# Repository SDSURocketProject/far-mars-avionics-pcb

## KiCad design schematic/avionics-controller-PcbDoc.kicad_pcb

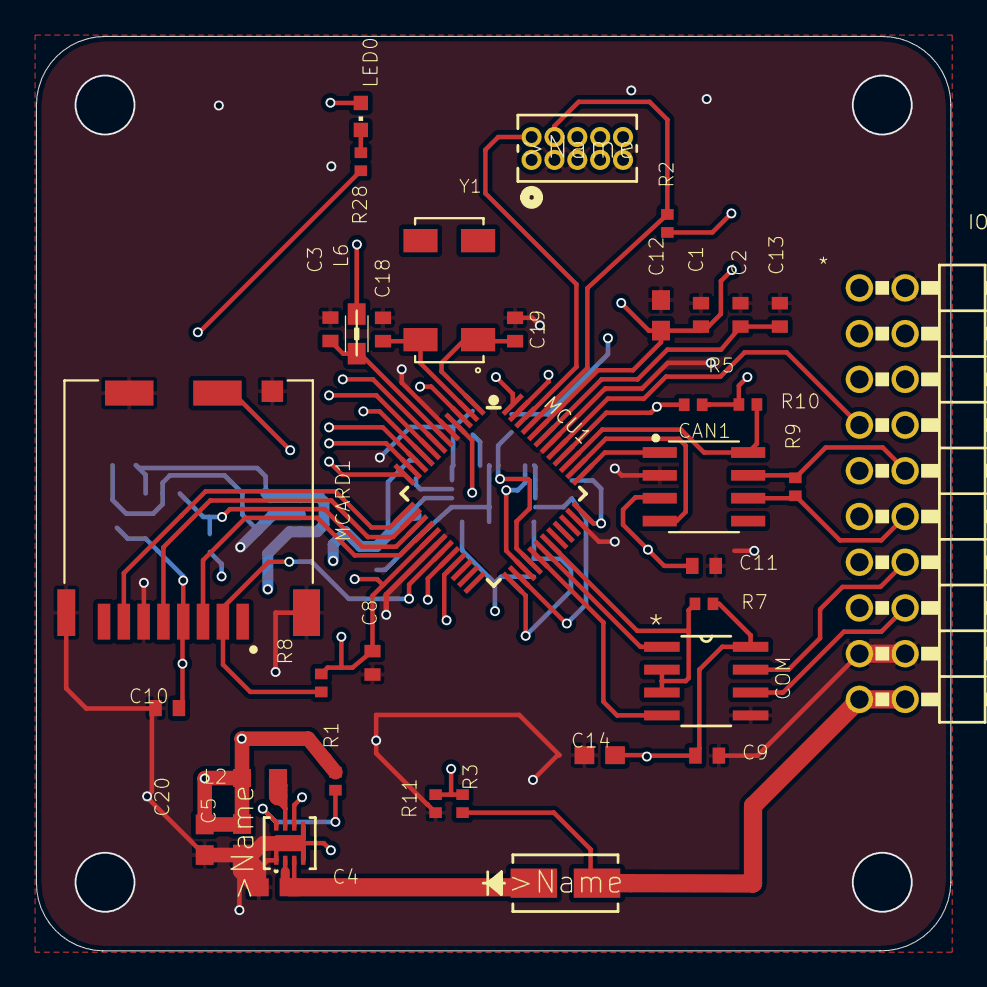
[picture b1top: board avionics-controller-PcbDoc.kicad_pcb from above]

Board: 4 copper layers, 50.8 x 50.8 mm, 52 parts (0 on the bottom side), 51 nets.

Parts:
3VREG1, 3VREG-SD1: 3.3VREGULATOR; SOT95P280X110-5
C1, C2, C3, C8, C9, C10, C11, C15, C16: 100n; C0402
C4, C5, C12, C14, C20: 10u; C0603
C6, C7, C13, C17, C21: 1u; C0402
C18, C19: 15p; C0402
CAN1: MCP2561T-E8SOIC; SOIC127P600X175-8
CR1: B160-13-FSMA-M; SMA-M
IMU1: BNO055; LGA28R50P4X10_380X520X100
IO1: PINHD-2X10_90; 2X10_90
L2: 2.2u; L2012C
L6: MH2029-300Y; 0805
LED0: 2V @ 20mA; CHIPLED_0603
MCARD1: DM3CS-SF; HRS_DM3CS-SF
MCU1: ATSAMC21G18-A; TQFP-48
R1: 100k; R0402
R2, R11, R38, R39: 1k; R0402
R3, R4, R5, R6, R7, R8, R10, R12: 10k; R0402
R9, R28: 120; R0402
REG5V1: TPS62163DSGT; DSG8_1P6X0P9
SWD1: DEBUG-HEADER; CONN_MINITEK_2X5_HDR
U1: SN65HVD10_D_8; D8
U$6: RP-LOGO
Y1: ABS25-32.768KHZ; ABS25-32.768KHZ-6-T

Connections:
3.3V: 3VREG1.5, C6.1, C8.1, C9.1, C14.1, C15.1, IMU1.3, IMU1.28, LED0.A, MCU1.17, MCU1.36, R4.1, R6.1, R7.1, R8.1, R38.1, R39.1, U1.8
5V: 3VREG1.1, 3VREG1.3, 3VREG-SD1.1, C1.1, C5.1, C7.1, C11.1, C12.1, C20.1, C21.1, CAN1.3, IO1.1, L2.2, L6.1, MCU1.44, R1.2, R2.1, R5.1, R10.1, R12.1, REG5V1.6, SWD1.1
/avionics-controller_1/3V_SD: 3VREG-SD1.5, C10.1, C17.1, MCARD1.4
/avionics-controller_1/A: IO1.16, U1.6
/avionics-controller_1/B: IO1.14, U1.7
/avionics-controller_1/CANH: CAN1.7, IO1.10, R9.2
/avionics-controller_1/CANL: CAN1.6, IO1.12, R9.1
/avionics-controller_1/CAN_RX_5V: CAN1.4, MCU1.38
/avionics-controller_1/CAN_STBY_5V: CAN1.8, MCU1.39, R10.2
/avionics-controller_1/CAN_TX_5V: CAN1.1, MCU1.37
/avionics-controller_1/DATA_DIR: MCU1.31, R7.2, U1.2, U1.3
/avionics-controller_1/IMU_INT: IMU1.14, MCU1.27
/avionics-controller_1/IMU_NRST: IMU1.11, MCU1.28, R4.2
/avionics-controller_1/LED0: MCU1.21, R28.1
/avionics-controller_1/MCU_NRST: MCU1.40, R5.2, SWD1.10
/avionics-controller_1/MCU_RX_3.3V: MCU1.30, U1.1
/avionics-controller_1/MCU_TX_3.3V: MCU1.29, U1.4
/avionics-controller_1/PA02/AIN0: IO1.5, MCU1.3
/avionics-controller_1/PA04/AIN4: IO1.9, MCU1.9
/avionics-controller_1/PA05/AIN5: IO1.11, MCU1.10
/avionics-controller_1/PA06/AIN6: IO1.13, MCU1.11
/avionics-controller_1/PA07/AIN7: IO1.15, MCU1.12
/avionics-controller_1/PA16_SER1_I2C_SDA: IMU1.20, MCU1.25, R38.2
/avionics-controller_1/PA17_SER1_I2C_SCL: IMU1.19, MCU1.26, R39.2
/avionics-controller_1/PA28: IO1.7, MCU1.41
/avionics-controller_1/PB02/AIN10: IO1.3, MCU1.47
/avionics-controller_1/PB03/AIN11: IO1.4, MCU1.48
/avionics-controller_1/PB08/AIN2: IO1.6, MCU1.7
/avionics-controller_1/PB09/AIN3: IO1.8, MCU1.8
/avionics-controller_1/SD_CD: MCARD1.9, MCU1.20
/avionics-controller_1/SD_CS: MCARD1.2, MCU1.19, R8.2
/avionics-controller_1/SD_EN: 3VREG-SD1.3, MCU1.15, R12.2
/avionics-controller_1/SER0_P0_DI: MCARD1.7, MCU1.13
/avionics-controller_1/SER0_P1_CLK: MCARD1.5, MCU1.14
/avionics-controller_1/SER0_P3_DO: MCARD1.3, MCU1.16
/avionics-controller_1/SWCLK: MCU1.45, R2.2, SWD1.4
/avionics-controller_1/SWDIO: MCU1.46, SWD1.2
/avionics-controller_1/VBAT_SENSE: MCU1.4, R3.1, R11.2
/avionics-controller_1/VDDCORE: C2.1, C13.1, MCU1.43
GND: 3VREG1.2, 3VREG-SD1.2, C1.2, C2.2, C3.1, C4.2, C5.2, C6.2, C7.2, C8.2, C9.2, C10.2, C11.2, C12.2, C13.2, C14.2, C15.2, C16.2, C17.2, C18.2, C19.2, C20.2, C21.2, CAN1.2, IMU1.2, IMU1.5, IMU1.6, IMU1.10, IMU1.15, IMU1.16, IMU1.17, IMU1.18, IMU1.25, IO1.2, IO1.17, IO1.18, MCARD1.6, MCARD1.S1, MCARD1.S2, MCARD1.S3, MCARD1.S5, MCU1.5, MCU1.18, MCU1.35, MCU1.42, R11.1, REG5V1.1, SWD1.3, SWD1.5, SWD1.9, U1.5
unnamed: C3.2, L6.2, MCU1.6
unnamed: C4.1, CR1.1, REG5V1.2, REG5V1.3
unnamed: C16.1, IMU1.9
unnamed: C18.1, MCU1.2, Y1.4
unnamed: C19.1, MCU1.1, Y1.1
unnamed: IMU1.4, R6.2
unnamed: L2.1, REG5V1.7
unnamed: LED0.C, R28.2
unnamed: R1.1, REG5V1.8
unnamed: REG5V1.4, REG5V1.5, REG5V1.9
V_BATT: CR1.2, IO1.19, IO1.20, R3.2

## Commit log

2020-07-26 moved schematic to kicad
